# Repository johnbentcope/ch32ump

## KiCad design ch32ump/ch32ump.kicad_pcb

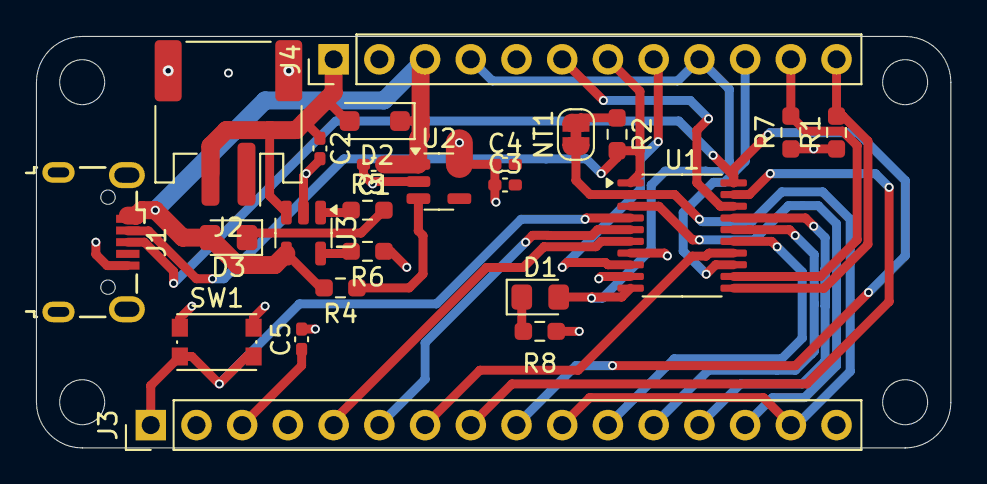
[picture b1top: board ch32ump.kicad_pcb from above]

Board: 4 copper layers, 50.8 x 22.9 mm, 24 parts (0 on the bottom side), 29 nets.

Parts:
C1, C2, C3: 10u; C_0402_1005Metric_Pad0.74x0.62mm_HandSolder
C4, C5: 1u; C_0402_1005Metric_Pad0.74x0.62mm_HandSolder
D1, D3: LED; LED_0805_2012Metric_Pad1.15x1.40mm_HandSolder
D2: MBR1020VL; D_SOD-123F
J1: USB_B_Micro; USB_Micro-B_Wuerth_629105150521
J2: Conn_01x02; JST_PH_S2B-PH-SM4-TB_1x02-1MP_P2.00mm_Horizontal
J3: Conn_01x16; PinHeader_1x16_P2.54mm_Vertical
J4: Conn_01x12; PinHeader_1x12_P2.54mm_Vertical
NT1: NetTie_2; SolderJumper-2_P1.3mm_Bridged_RoundedPad1.0x1.5mm
R1, R6, R7: 10k; R_0603_1608Metric_Pad0.98x0.95mm_HandSolder
R2: 1.5k; R_0603_1608Metric_Pad0.98x0.95mm_HandSolder
R4: 100k; R_0603_1608Metric_Pad0.98x0.95mm_HandSolder
R5: 1k; R_0603_1608Metric_Pad0.98x0.95mm_HandSolder
R8: 2.2k; R_0603_1608Metric_Pad0.98x0.95mm_HandSolder
SW1: SW_Push_Dual; SW_Push_1P1T_NO_CK_KMR2
U1: CH32V003F4P6; TSSOP-20_4.4x6.5mm_P0.65mm
U2: AP2112K-3.3; SOT-23-5
U3: MCP73831-2-OT; SOT-23-5

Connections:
+3.3V: C3.1, C4.1, J3.2, R1.1, R7.1, U1.9 (VDD), U2.5 (VOUT)
+BATT: C2.1, D2.2 (A), J2.2, J4.1, U3.3 (V_{BAT})
A3: J3.8, U1.19 (PD2)
AREF: C5.1, J3.3
D+: J1.3 (D+), J3.9, U1.20 (PD3)
D-: J1.2 (D-), J4.7, R2.1, U1.1 (PD4)
DPU: NT1.2, R2.2
GND: C1.2, C2.2, C3.2, C4.2, C5.2, J1.5 (GND), J2.1, J3.4, R6.1, R8.1, SW1.1, U1.7 (VSS), U2.2 (GND), U3.2 (V_{SS})
MI: J3.13, U1.17 (PC7)
MO: J3.12, U1.16 (PC6)
unnamed: D1.1 (K), R8.2
unnamed: D3.1 (K), R5.2
unnamed: R4.1, U2.3 (EN)
unnamed: R6.2, U3.5 (PROG)
unnamed: R5.1, U3.1 (STAT)
PA1: J3.6, U1.5 (PA1)
PA2: J3.5, U1.6 (PA2)
PC0: D1.2 (A), J4.4, J4.9, U1.10 (PC0)
PC3: J4.10, U1.13 (PC3)
PC4: J3.7, U1.14 (PC4)
PD0: J4.8, U1.8 (PD0)
SCK: J3.11, U1.15 (PC5)
SCL: J4.11, R7.2, U1.12 (PC2)
SDA: J4.12, R1.2, U1.11 (PC1)
SWIO: J4.6, U1.18 (PD1)
URX: J3.14, U1.3 (PD6)
UTX: J3.10, J3.15, NT1.1, U1.2 (PD5)
VBUS: C1.1, D2.1 (K), D3.2 (A), J1.1 (VBUS), J4.3, R4.2, U2.1 (VIN), U3.4 (V_{DD})
~RESET: J3.1, SW1.2, U1.4 (PD7)

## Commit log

2025-08-09 For the sake of my sanity, just ignore this...
2025-08-09 more fixes
2025-08-10 Saint Pipeline, please give me the green light
